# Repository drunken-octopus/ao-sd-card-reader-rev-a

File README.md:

# ao-sd-card-reader-rev-a
Revision A of the Aleph Objects SD card reader ("hidden"), copied from http://devel.lulzbot.com

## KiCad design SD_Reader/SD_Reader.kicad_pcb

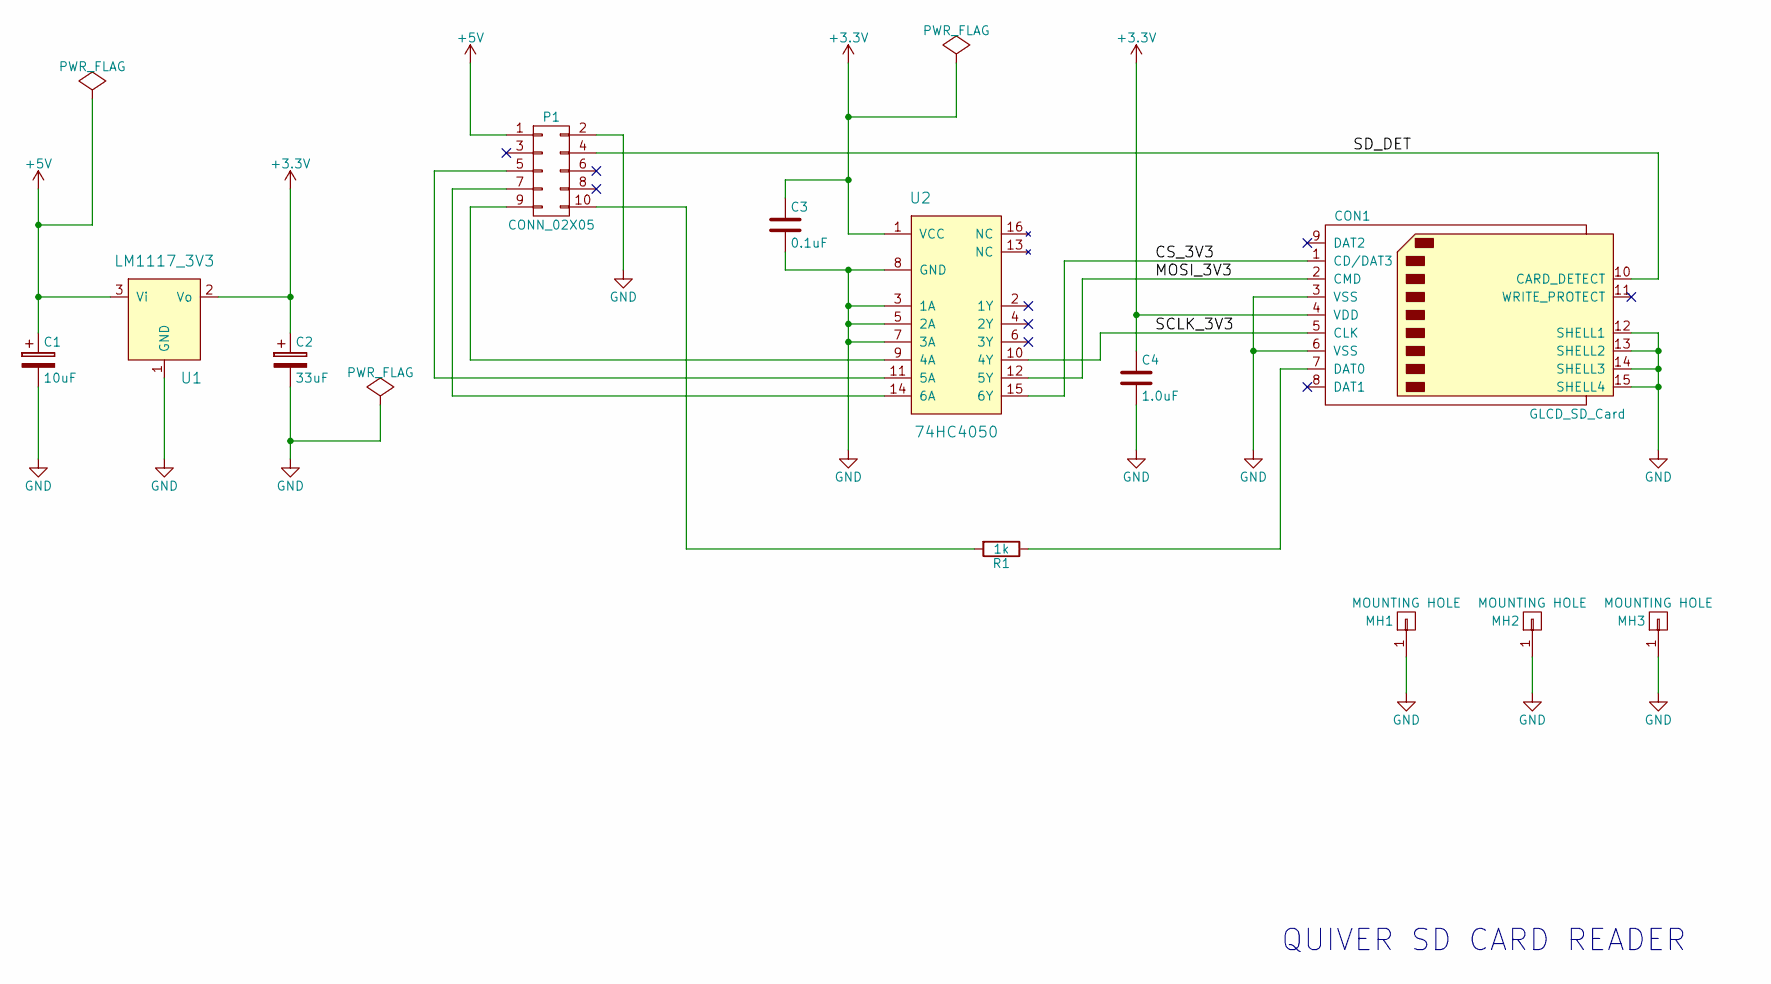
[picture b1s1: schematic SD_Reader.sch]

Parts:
C1: 10uF; TantalC_SizeD_EIA-7343_HandSoldering
C2: 33uF; TantalC_SizeD_EIA-7343_HandSoldering
C3: 0.1uF; C_0603_HandSoldering
C4: 1.0uF; C_0603_HandSoldering
CON1: GLCD_SD_Card; SD_Card_Receptacle
MH1, MH2, MH3: MOUNTING HOLE; MH_M3x6mm
P1: CONN_02X05; IDC_Header_Straight_10pins
R1: 1k; R_0603_HandSoldering
U1: LM1117_3V3; TO-252-2Lead
U2: 74HC4050; SO-16-N

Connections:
+3V3: C2.1, C3.1, C4.1, CON1.4 (VDD), U1.2 (Vo), U2.1 (VCC)
+5V: C1.1, P1.1, U1.3 (Vi)
/CS_3V3: CON1.1 (CD/DAT3), U2.15 (6Y)
/MOSI_3V3: CON1.2 (CMD), U2.12 (5Y)
/SCLK_3V3: CON1.5 (CLK), U2.10 (4Y)
/SD_DET: CON1.10 (CARD_DETECT), P1.4
GND: C1.2, C2.2, C3.2, C4.2, CON1.3 (VSS), CON1.6 (VSS), CON1.12 (SHELL1), CON1.13 (SHELL2), CON1.14 (SHELL3), CON1.15 (SHELL4), MH1.1, MH2.1, MH3.1, P1.2, U1.1 (GND), U2.3 (1A), U2.5 (2A), U2.7 (3A), U2.8 (GND)
unnamed: CON1.7 (DAT0), R1.1
unnamed: P1.5, U2.11 (5A)
unnamed: P1.7, U2.14 (6A)
unnamed: P1.9, U2.9 (4A)
unnamed: P1.10, R1.2

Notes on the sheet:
QUIVER SD CARD READER

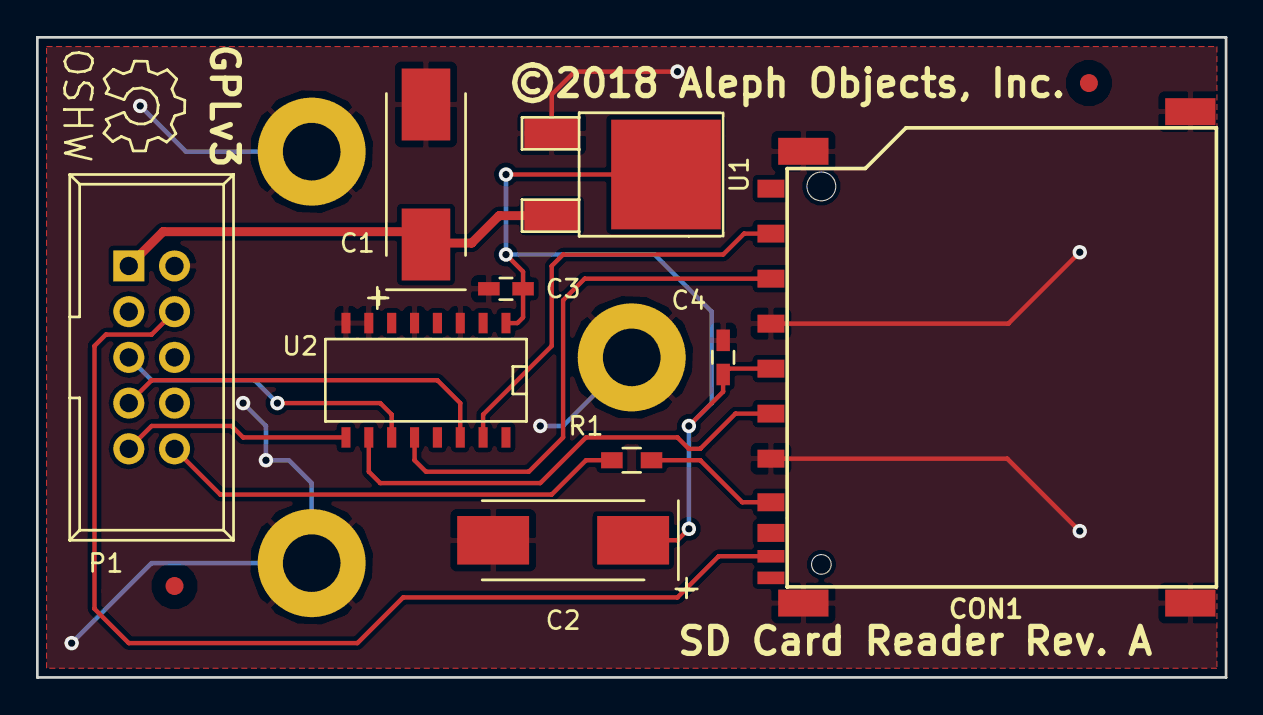
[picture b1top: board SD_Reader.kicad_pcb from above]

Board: 2 copper layers, 66.0 x 35.6 mm, 12 parts (0 on the bottom side), 12 nets.

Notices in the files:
SD_Reader/SD_Reader.kicad_pcb:
GPLv3
©2018 Aleph Objects, Inc.
